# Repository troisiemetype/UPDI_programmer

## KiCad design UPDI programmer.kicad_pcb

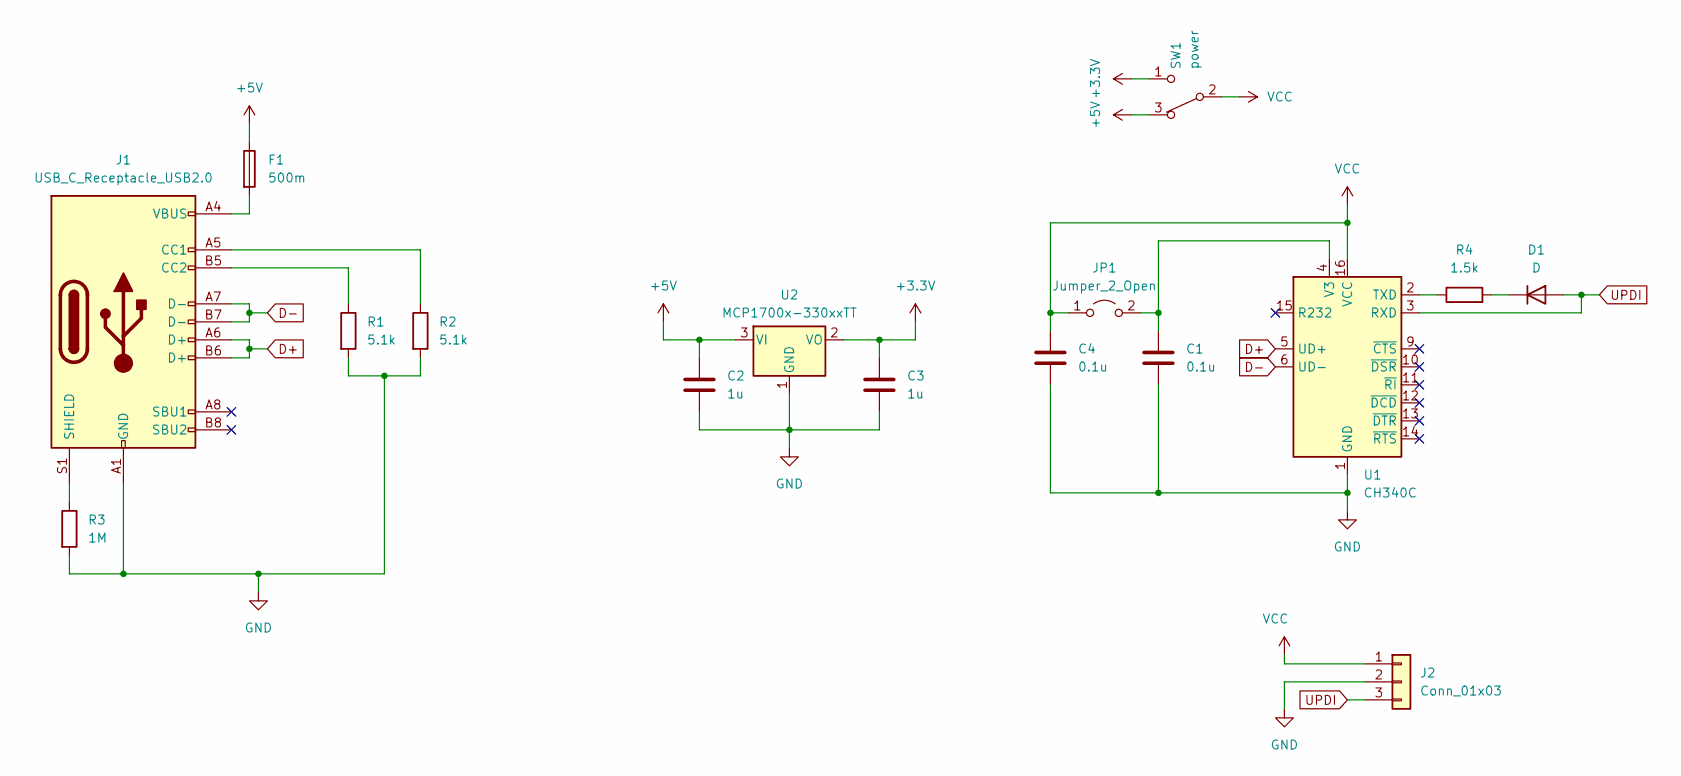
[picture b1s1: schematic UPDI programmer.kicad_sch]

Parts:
C1, C4: 0.1u; C_0603_1608Metric_Pad1.08x0.95mm_HandSolder
C2, C3: 1u; C_0603_1608Metric_Pad1.08x0.95mm_HandSolder
D1: D; D_SOD-123
F1: 500m; Fuse_1206_3216Metric
J1: USB_C_Receptacle_USB2.0; USB_C_Receptacle_GCT_USB4085
J2: Conn_01x03; Connector_pad_1x03_L10_P2.54mm
JP1: Jumper_2_Open; SolderJumper-2_P1.3mm_Open_RoundedPad1.0x1.5mm
R1, R2: 5.1k; R_0603_1608Metric_Pad0.98x0.95mm_HandSolder
R3: 1M; R_0603_1608Metric_Pad0.98x0.95mm_HandSolder
R4: 1.5k; R_0603_1608Metric_Pad0.98x0.95mm_HandSolder
SW1: power; SW_CuK_OS102011MA1QN1_SPDT_Angled
U1: CH340C; SOIC-16_3.9x9.9mm_P1.27mm
U2: MCP1700x-330xxTT; SOT-23

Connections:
+3.3V: C3.1, SW1.1 (C), U2.2 (VO)
+5V: C2.1, F1.1, SW1.3 (A), U2.3 (VI)
D+: J1.A6 (D+), J1.B6 (D+), U1.5 (UD+)
D-: J1.A7 (D-), J1.B7 (D-), U1.6 (UD-)
GND: C1.2, C2.2, C3.2, C4.2, J1.A1 (GND), J1.A12 (GND), J1.B1 (GND), J1.B12 (GND), J2.2, R1.2, R2.2, R3.2, U1.1 (GND), U2.1 (GND)
unnamed: D1.1 (K), R4.2
unnamed: F1.2, J1.A4 (VBUS), J1.A9 (VBUS), J1.B4 (VBUS), J1.B9 (VBUS)
unnamed: J1.A5 (CC1), R2.1
unnamed: J1.B5 (CC2), R1.1
unnamed: J1.S1 (SHIELD), R3.1
unnamed: C1.1, JP1.2 (B), U1.4 (V3)
unnamed: R4.1, U1.2 (TXD)
UPDI: D1.2 (A), J2.3, U1.3 (RXD)
VCC: C4.1, J2.1, JP1.1 (A), SW1.2 (B), U1.16 (VCC)

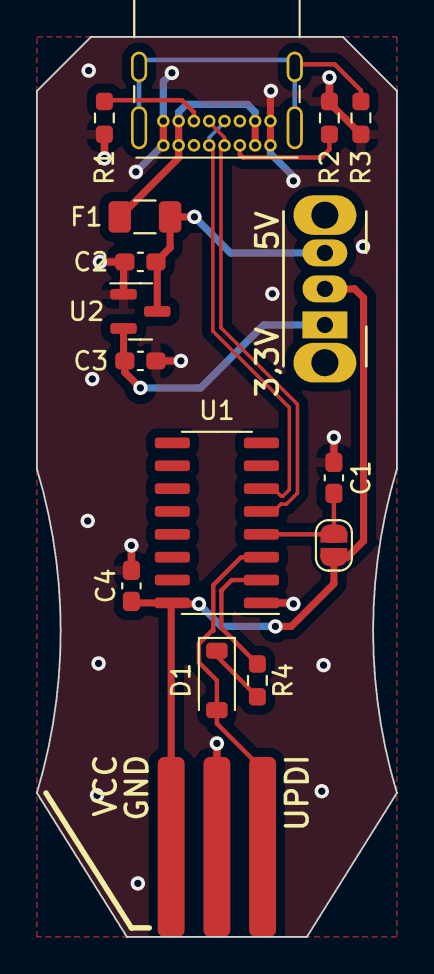
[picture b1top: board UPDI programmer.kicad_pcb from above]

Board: 2 copper layers, 20.0 x 50.0 mm, 16 parts (0 on the bottom side), 14 nets.

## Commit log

2023-12-24 Initial commit. PCB seems ok, still need reviewing.
2023-12-24 Added panelization files (but there's a problem with tabs. Added fabrication files.
2023-12-26 Added version on bottom silk.
2024-01-09 Added components table. v1.0 sent to fab.
